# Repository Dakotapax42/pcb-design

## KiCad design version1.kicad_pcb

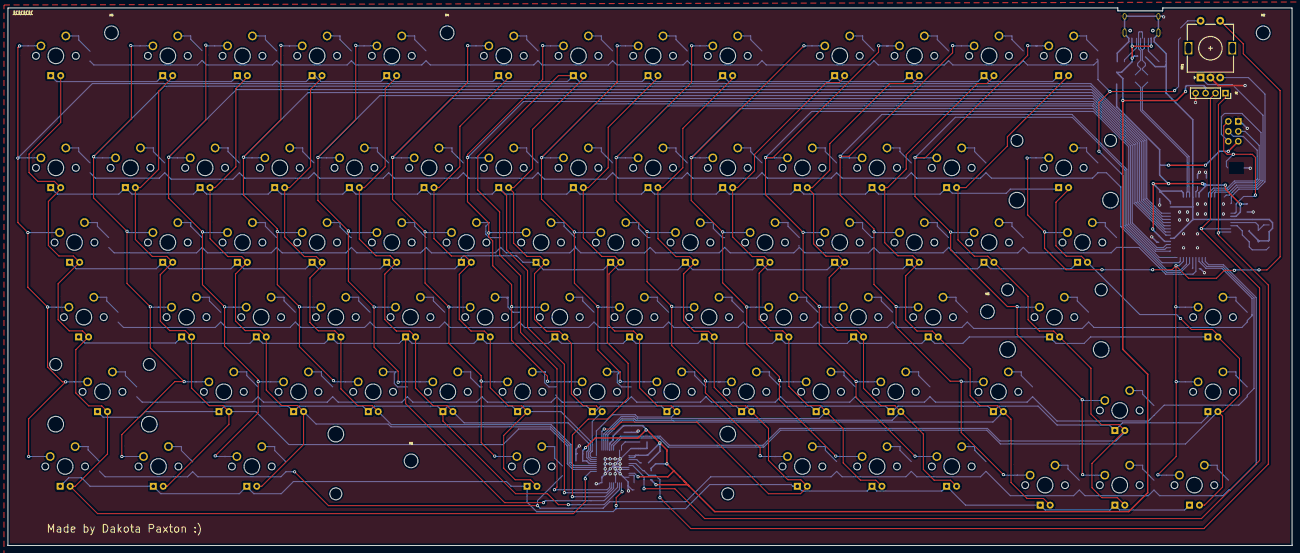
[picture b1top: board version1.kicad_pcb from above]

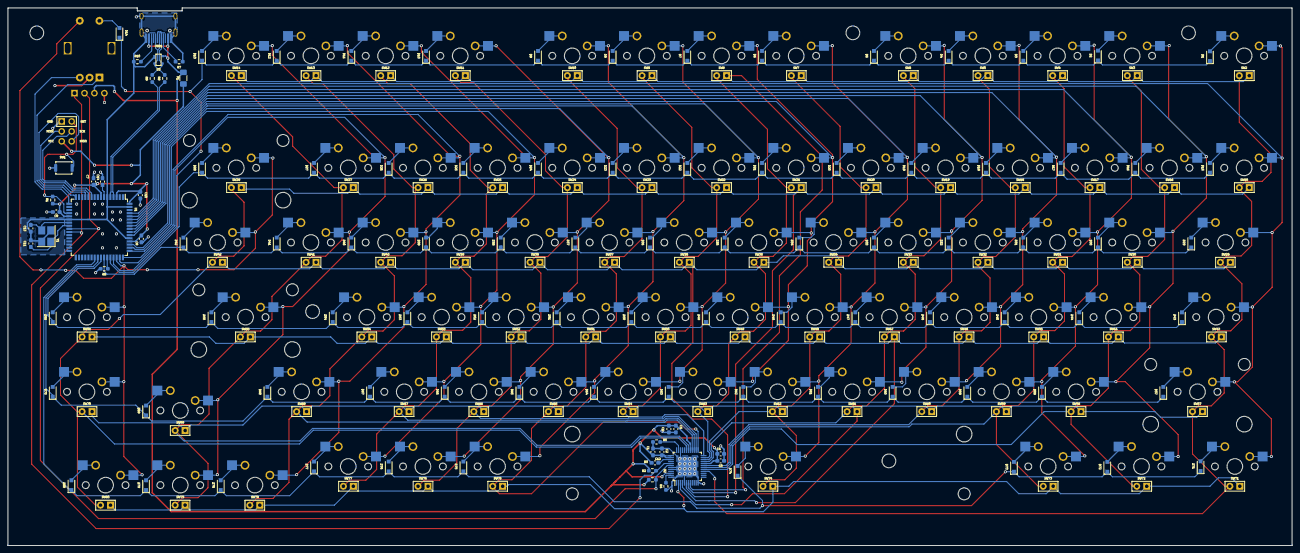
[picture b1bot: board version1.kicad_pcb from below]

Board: 2 copper layers, 327.7 x 137.2 mm, 277 parts (112 on the bottom side), 144 nets.

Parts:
C1, C3, C5, C12: .47uF; C_0603_1608Metric_Pad1.08x0.95mm_HandSolder
C2, C4, C6: .1uF; C_0603_1608Metric_Pad1.08x0.95mm_HandSolder
C7, C8, C9: 0.1uF; C_0603_1608Metric_Pad1.08x0.95mm_HandSolder
C10: 10uF; C_0603_1608Metric_Pad1.08x0.95mm_HandSolder
C11, C13: 22pF; C_0603_1608Metric_Pad1.08x0.95mm_HandSolder
C14: 1uF; C_0603_1608Metric_Pad1.08x0.95mm_HandSolder
D1, D2, D3, D4, D5, D6, D7, D8, D9, D10, D11, D12, D13, D14, D15, D16, D17, D18, D19, D20, D21, D22, D23, D24, D25, D26, D27, D28, D29, D30, D31, D32, D33, D34, D35, D36, D37, D38, D39, D40, D41, D42, D43, D44, D45, D46, D47, D48, D49, D50, D51, D52, D53, D54, D55, D56, D57, D58, D59, D60, D61, D62, D63, D64, D65, D66, D67, D68, D69, D70, D71, D72, D73, D74, D75, D76, D77, D78, D79, D80: D_Small; D_SOD-323_HandSoldering
D81, D82, D83, D84, D85, D86, D87, D88, D89, D90, D91, D92, D93, D94, D95, D96, D97, D98, D99, D100, D101, D102, D103, D104, D105, D106, D107, D108, D109, D110, D111, D112, D113, D114, D115, D116, D117, D118, D119, D120, D121, D122, D123, D124, D125, D126, D127, D128, D129, D130, D131, D132, D133, D134, D135, D136, D137, D138, D139, D140, D141, D142, D143, D144, D145, D146, D147, D148, D149, D150, D151, D152, D153, D154, D155, D156, D157, D158, D159: LED_Small; LED_D3.0mm-NoSilk
F1: 500m; Fuse_1206_3216Metric_Pad1.42x1.75mm_HandSolder
H1, H2, H3, H4, H5: MountingHole; MountingHole_3.5mm
J1: AVR-ISP-6; Reset_Pretty-Mask
J2: Conn_01x04; PinSocket_1x04_P2.54mm_Vertical
R1: 10k; R_0603_1608Metric_Pad0.98x0.95mm_HandSolder
R2, R3, R6: 1k; R_0603_1608Metric_Pad0.98x0.95mm_HandSolder
R4: 100k; R_0603_1608Metric_Pad0.98x0.95mm_HandSolder
R5: 20k; R_0603_1608Metric_Pad0.98x0.95mm_HandSolder
R7, R10: 5k1; R_0603_1608Metric_Pad0.98x0.95mm_HandSolder
R8, R9: 22; R_0603_1608Metric_Pad0.98x0.95mm_HandSolder
RE1: Rotary_Encoder_Switch; RotaryEncoder_Alps_EC11E-Switch_Vertical_H20mm
SW1: SW_Push; SW_Push_SPST_NO_Alps_SKRK
SW2, SW3, SW4, SW5, SW6, SW7, SW8, SW9, SW10, SW11, SW12, SW13, SW14, SW15, SW16, SW17, SW18, SW19, SW20, SW21, SW22, SW23, SW24, SW25, SW26, SW27, SW30, SW31, SW32, SW33, SW34, SW35, SW36, SW37, SW38, SW39, SW40, SW41, SW44, SW45, SW46, SW47, SW48, SW49, SW50, SW51, SW52, SW53, SW54, SW56, SW58, SW59, SW60, SW61, SW62, SW63, SW64, SW65, SW66, SW67, SW69, SW70, SW75, SW76, SW77, SW78, SW79, SW80: SW_Push; MXOnly-1U-Hotswap
SW28: SW_Push; MXOnly-2U-Hotswap
SW29, SW42: SW_Push; MXOnly-1.5U-Hotswap
SW43, SW68: SW_Push; MXOnly-1.75U-Hotswap
SW55, SW57: SW_Push; MXOnly-2.25U-Hotswap
SW71, SW72, SW73: SW_Push; MXOnly-1.25U-Hotswap
SW74: SW_Push; MXOnly-6.25U-Hotswap-ReversedStabilizers
U1: AT90USB1286-AU; TQFP-64_14x14mm_P0.8mm
U2: IS31FL3733-TQ; TQFP-48-1EP_7x7mm_P0.5mm_EP5x5mm
U3: PRTR5V0U2X; SOT143B
USB1: HRO-TYPE-C-31-M-12; HRO-TYPE-C-31-M-12-HandSoldering
Y1: 16Mhz; Crystal_SMD_3225-4Pin_3.2x2.5mm_HandSoldering

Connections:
+5V: C7.1, C8.1, C9.1, C10.1, F1.1, J1.2, R1.1, U1.3, U1.8, U1.21, U1.52, U1.64
A1: RE1.A, U1.16
B1: RE1.B, U1.17
CS1: D81.2, D94.2, D108.2, D122.2, D136.2, D150.2, U2.16
CS2: D82.2, D95.2, D109.2, D123.2, D137.2, D151.2, U2.17
CS3: D83.2, D96.2, D110.2, D124.2, D138.2, D152.2, U2.18
CS4: D84.2, D97.2, D111.2, D125.2, D139.2, U2.19
CS5: D85.2, D98.2, D112.2, D126.2, D140.2, U2.21
CS6: D86.2, D99.2, D113.2, D127.2, D141.2, D153.2, U2.22
CS7: D87.2, D100.2, D114.2, D128.2, D142.2, U2.23
CS8: D88.2, D101.2, D115.2, D129.2, D143.2, U2.24
CS9: D89.2, D102.2, D116.2, D130.2, D144.2, D154.2, U2.25
CS10: D90.2, D103.2, D117.2, D131.2, D145.2, D155.2, U2.26
CS11: D91.2, D104.2, D118.2, D132.2, D146.2, D156.2, U2.27
CS12: D92.2, D105.2, D119.2, D133.2, D147.2, D157.2, U2.28
CS13: D93.2, D106.2, D120.2, D134.2, D148.2, D158.2, U2.30
CS14: D107.2, D121.2, D135.2, D149.2, D159.2, U2.31
D+: R9.1, U1.5
D-: R8.1, U1.4
DN: R8.2, U3.3, USB1.5, USB1.7
DP: R9.2, U3.2, USB1.6, USB1.8
GND: C1.2, C2.2, C3.2, C4.2, C5.2, C6.2, C7.2, C8.2, C9.2, C10.2, C11.2, C13.2, C14.2, J1.6, J2.4, R4.2, R5.2, R6.2, R7.1, R10.1, RE1.C, SW1.1, U1.6, U1.22, U1.53, U1.63, U2.5, U2.12, U2.34, U2.43, U2.44, U2.48, U2.49, U3.1, USB1.1, USB1.12, USB1.13, Y1.2, Y1.4
unnamed: C11.1, U1.24, Y1.1
unnamed: C12.2, U2.39
unnamed: C13.1, U1.23, Y1.3
unnamed: C14.1, U1.7
unnamed: D1.2, SW2.2
unnamed: D2.2, SW3.2
unnamed: D3.2, SW4.2
unnamed: D4.2, SW5.2
unnamed: D5.2, SW6.2
unnamed: D6.2, SW7.2
unnamed: D7.2, SW8.2
unnamed: D8.2, SW9.2
unnamed: D9.2, SW10.2
unnamed: D10.2, SW11.2
unnamed: D11.2, SW12.2
unnamed: D12.2, SW13.2
unnamed: D13.2, SW14.2
unnamed: D14.2, RE1.S2
unnamed: D15.2, SW15.2
unnamed: D16.2, SW16.2
unnamed: D17.2, SW17.2
unnamed: D18.2, SW18.2
unnamed: D19.2, SW19.2
unnamed: D20.2, SW20.2
unnamed: D21.2, SW21.2
unnamed: D22.2, SW22.2
unnamed: D23.2, SW23.2
unnamed: D24.2, SW24.2
unnamed: D25.2, SW25.2
unnamed: D26.2, SW26.2
unnamed: D27.2, SW27.2
unnamed: D28.2, SW28.2
unnamed: D29.2, SW29.2
unnamed: D30.2, SW30.2
unnamed: D31.2, SW31.2
unnamed: D32.2, SW32.2
unnamed: D33.2, SW33.2
unnamed: D34.2, SW34.2
unnamed: D35.2, SW35.2
unnamed: D36.2, SW36.2
unnamed: D37.2, SW37.2
unnamed: D38.2, SW38.2
unnamed: D39.2, SW39.2
unnamed: D40.2, SW40.2
unnamed: D41.2, SW41.2
unnamed: D42.2, SW42.2
unnamed: D43.2, SW43.2
unnamed: D44.2, SW44.2
unnamed: D45.2, SW45.2
unnamed: D46.2, SW46.2
unnamed: D47.2, SW47.2
unnamed: D48.2, SW48.2
unnamed: D49.2, SW49.2
unnamed: D50.2, SW50.2
unnamed: D51.2, SW51.2
unnamed: D52.2, SW52.2
unnamed: D53.2, SW53.2
unnamed: D54.2, SW54.2
unnamed: D55.2, SW55.2
unnamed: D56.2, SW56.2
unnamed: D57.2, SW57.2
unnamed: D58.2, SW58.2
unnamed: D59.2, SW59.2
unnamed: D60.2, SW60.2
unnamed: D61.2, SW61.2
unnamed: D62.2, SW62.2
unnamed: D63.2, SW63.2
unnamed: D64.2, SW64.2
unnamed: D65.2, SW65.2
unnamed: D66.2, SW66.2
unnamed: D67.2, SW67.2
unnamed: D68.2, SW68.2
unnamed: D69.2, SW69.2
unnamed: D70.2, SW70.2
unnamed: D71.2, SW71.2
unnamed: D72.2, SW72.2
unnamed: D73.2, SW73.2
unnamed: D74.2, SW74.2
unnamed: D75.2, SW75.2
unnamed: D76.2, SW76.2
unnamed: D77.2, SW77.2
unnamed: D78.2, SW78.2
unnamed: D79.2, SW79.2
unnamed: D80.2, SW80.2
unnamed: J1.1, U1.13
unnamed: J1.3, U1.11
unnamed: J1.4, U1.12
unnamed: R4.1, U2.47
unnamed: R5.1, U2.35
unnamed: R6.1, U1.43
unnamed: R7.2, USB1.4
unnamed: R10.2, USB1.10
RESET: J1.5, R1.2, SW1.2, U1.20
SCL: J2.2, R2.2, U1.25, U2.42
SDA: J2.1, R3.2, U1.26, U2.41
SW1: D150.1, D151.1, D152.1, D153.1, D154.1, D155.1, D156.1, D157.1, D158.1, D159.1, U2.2
SW2: D136.1, D137.1, D138.1, D139.1, D140.1, D141.1, D142.1, D143.1, D144.1, D145.1, D146.1, D147.1, D148.1, D149.1, U2.3
SW3: D122.1, D123.1, D124.1, D125.1, D126.1, D127.1, D128.1, D129.1, D130.1, D131.1, D132.1, D133.1, D134.1, D135.1, U2.4
SW4: D108.1, D109.1, D110.1, D111.1, D112.1, D113.1, D114.1, D115.1, D116.1, D117.1, D118.1, D119.1, D120.1, D121.1, U2.6
SW5: D94.1, D95.1, D96.1, D97.1, D98.1, D99.1, D100.1, D101.1, D102.1, D103.1, D104.1, D105.1, D106.1, D107.1, U2.7
SW6: D81.1, D82.1, D83.1, D84.1, D85.1, D86.1, D87.1, D88.1, D89.1, D90.1, D91.1, D92.1, D93.1, U2.8
VCC: C1.1, C2.1, C3.1, C4.1, C5.1, C6.1, C12.1, F1.2, J2.3, R2.1, R3.1, U2.20, U2.29, U2.37, U2.38, U2.46, U3.4, USB1.2, USB1.11
col0: SW2.1, SW15.1, SW29.1, SW43.1, SW57.1, SW71.1, U1.61
col1: SW3.1, SW16.1, SW30.1, SW44.1, SW58.1, SW72.1, U1.60
col2: SW4.1, SW17.1, SW31.1, SW45.1, SW59.1, SW73.1, U1.59
col3: SW5.1, SW18.1, SW32.1, SW46.1, SW60.1, U1.58
col4: SW6.1, SW19.1, SW33.1, SW47.1, SW61.1, U1.57
col5: SW7.1, SW20.1, SW34.1, SW48.1, SW62.1, SW74.1, U1.56
col6: SW8.1, SW21.1, SW35.1, SW49.1, SW63.1, U1.55
col7: SW9.1, SW22.1, SW36.1, SW50.1, SW64.1, U1.54
col8: SW10.1, SW23.1, SW37.1, SW51.1, SW65.1, SW75.1, U1.51
col9: SW11.1, SW24.1, SW38.1, SW52.1, SW66.1, SW76.1, U1.50
col10: SW12.1, SW25.1, SW39.1, SW53.1, SW67.1, SW77.1, U1.49
col11: SW13.1, SW26.1, SW40.1, SW54.1, SW68.1, SW78.1, U1.48
col12: SW14.1, SW27.1, SW41.1, SW55.1, SW69.1, SW79.1, U1.47
col13: RE1.S1, SW28.1, SW42.1, SW56.1, SW70.1, SW80.1, U1.46
row0: D1.1, D2.1, D3.1, D4.1, D5.1, D6.1, D7.1, D8.1, D9.1, D10.1, D11.1, D12.1, D13.1, D14.1, U1.45
row1: D15.1, D16.1, D17.1, D18.1, D19.1, D20.1, D21.1, D22.1, D23.1, D24.1, D25.1, D26.1, D27.1, D28.1, U1.44
row2: D29.1, D30.1, D31.1, D32.1, D33.1, D34.1, D35.1, D36.1, D37.1, D38.1, D39.1, D40.1, D41.1, D42.1, U1.42
row3: D43.1, D44.1, D45.1, D46.1, D47.1, D48.1, D49.1, D50.1, D51.1, D52.1, D53.1, D54.1, D55.1, D56.1, U1.41
row4: D57.1, D58.1, D59.1, D60.1, D61.1, D62.1, D63.1, D64.1, D65.1, D66.1, D67.1, D68.1, D69.1, D70.1, U1.40
row5: D71.1, D72.1, D73.1, D74.1, D75.1, D76.1, D77.1, D78.1, D79.1, D80.1, U1.39

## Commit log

2021-03-19 step 1
    Setting up things
2021-03-19 Add submodules
2021-03-19 footprint libraries
2021-03-20 added type c port
2021-07-19 Final version
